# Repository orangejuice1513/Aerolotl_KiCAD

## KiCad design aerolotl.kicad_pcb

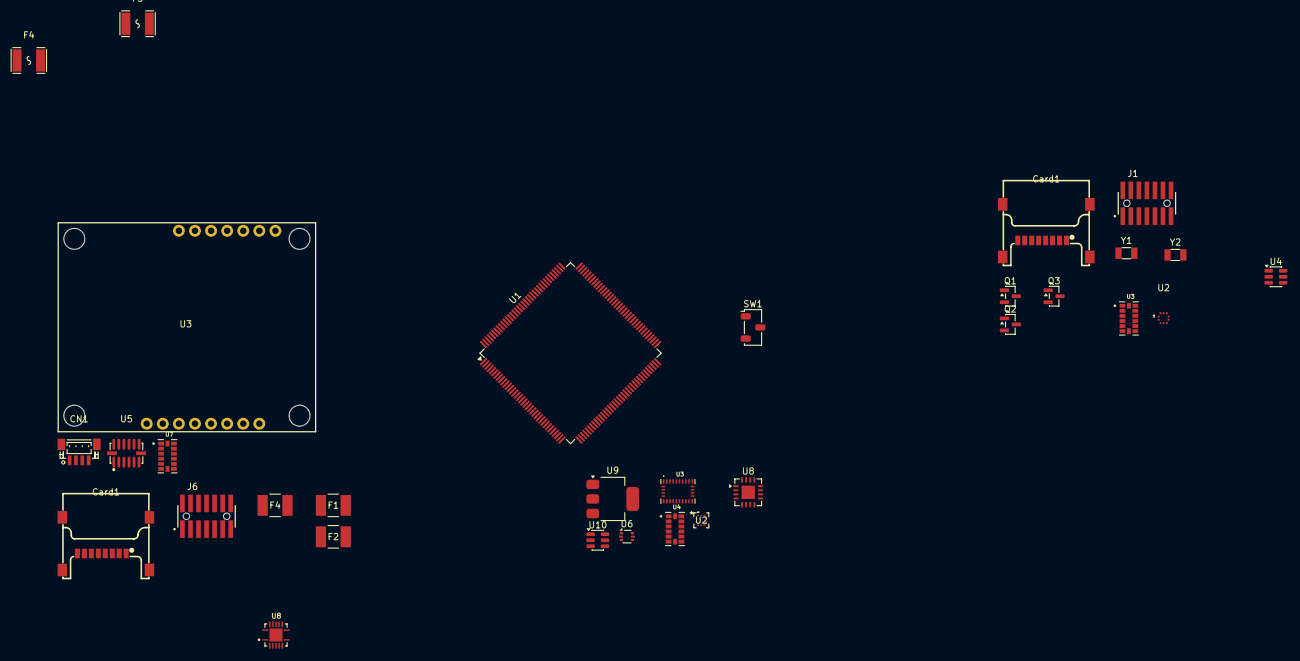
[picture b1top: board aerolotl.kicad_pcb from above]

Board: 2 copper layers, 31 parts (0 on the bottom side), 33 nets, no tracks yet.

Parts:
CN1: StemmaQT; CONN-SMD_BM04B-SRSS-TB
Card1: TF-102-15_SD_read; TF-SMD_TF-102-15
Card1#2: TF-102-15; TF-SMD_TF-102-15
F1, F2, F4#2: 1812L150/24MR; FUSE_1812L150&slash_24_LTF
F3, F4: 1812L300/24SLER; F1812
J1: SWD; SAMTEC_FTSH-107-01-L-DV-K-A
J6: FTSH-107-STDC14; SAMTEC_FTSH-107-01-L-DV-K-A
Q1, Q2, Q3: AO3400A; SOT-23
SW1: SW_Nidec_CAS-120A1; Nidec_Copal_CAS-120A
U1: STM32H755ZIT6; LQFP-144_20x20mm_P0.5mm
U2: BMP581; LGA-10_L2.0-W2.0-P0.50-TL_BMP581
U2#2: BMP581; QFN10_BMP581_BOS
U3: BNO085; IC_BNO085
U3#2, U4#2: ADXL345BCCZ-RL7; PQFN80P500X300X100-14N
U3#3: SparkfunM9N
U4, U10: LMR51430XFDDCR; SOT-23-6
U5: ADXL375BCCZ-RL7; LGA-14_L5.0-W3.0-P0.80-BL
U6: USBLC6-2P6; SOT-666
U7: ADXL345BCCZ-RL7; ADXL345
U8: TPS54620RGYR; TPS54620_7v4buck
U8#2: FT230XQ; QFN-16-1EP_4x4mm_P0.65mm_EP2.1x2.1mm
U9: AMS1117-3.3; SOT-223-3_TabPin2
Y1: 25M; Crystal_SMD_3215-2Pin_3.2x1.5mm
Y2: 32k768; Crystal_SMD_3215-2Pin_3.2x1.5mm

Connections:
+3V3: Card1.4 (VDD), Card1#2.4 (VDD), J6.03, SW1.3 (A), U1.7 (VDD), U1.8 (VBAT), U1.13 (VDD), U1.16 (VDDSMPS), U1.19 (VDD), U1.32 (VDD), U1.42 (VDD), U1.56 (VDD), U1.70 (VDDLDO), U1.71 (VDD), U1.79 (VDD), U1.90 (VDD50_USB), U1.91 (VDD33_USB), U1.92 (VDD), U1.105 (VDDLDO), U1.106 (VDD), U1.119 (VDD), U1.129 (VDD), U1.142 (PDR_ON), U1.143 (VDDLDO), U1.144 (VDD), U3#3.6 (3V3), U3#3.11 (3V3)
+7V4_SERVO: F3.1, F4.1
+12V: U4.3 (VIN), U4.5 (EN)
+12V_ARM: F1.2, F2.2
/Debugger/T_SWCLK: J1.06, J6.06, U1.107 (PA14)
/Debugger/T_SWDIO: J1.04, J6.04, U1.102 (PA13)
/Debugger/T_SWO: J1.08, J6.08, U1.130 (PB3)
/Debugger/T_VCP_RX: J1.14, J6.14, U1.98 (PA9)
/Debugger/T_VCP_TX: J1.13, J6.13, U1.99 (PA10)
/IMUs/ADXL345.CS: U3#2.7 (~CS), U7.7 (~CS)
/IMUs/ADXL345.SCLK: U1.44 (PA5), U2.2 (SCK), U3#2.14 (SCL/SCLK), U5.14 (SCL/SCLK), U7.14 (SCL/SCLK)
/IMUs/ADXL345.SDI: U1.45 (PA6), U2.5 (SDO), U3#2.13 (SDA/SDI/SDIO), U5.12 (SDO/ALTADDRESS), U7.13 (SDA/SDI/SDIO)
/IMUs/ADXL345.SDO: U1.46 (PA7), U2.4 (SDI), U3#2.12 (SDO/ALT_ADDRESS), U5.13 (SDA/SDI/SDIO), U7.12 (SDO/ALT_ADDRESS)
/MCU/BOOT0: SW1.2 (B), U1.135 (BOOT0)
/MCU/HS_OSC_A: U1.25 (PH0), Y1.1
/MCU/HS_OSC_B: U1.26 (PH1), Y1.2
/MCU/LS_OSC_A: U1.10 (PC14), Y2.2
/MCU/LS_OSC_B: U1.11 (PC15), Y2.1
/MCU/RESET: J6.12, U1.27 (NRST)
/MCU/SDMMC1.CK: Card1.5 (CLK), Card1#2.5 (CLK), U1.111 (PC12)
/MCU/SDMMC1.CMD: Card1.3 (CMD), Card1#2.3 (CMD), U1.114 (PD2)
/MCU/SDMMC1.D0: Card1.7 (DAT0), Card1#2.7 (DAT0), U1.95 (PC8)
/MCU/SDMMC1.D1: Card1.8 (DAT1), Card1#2.8 (DAT1), U1.96 (PC9)
/MCU/SDMMC1.D2: Card1.1 (DAT2), Card1#2.1 (DAT2), U1.109 (PC10)
/MCU/SDMMC1.D3: Card1.2 (CD/DAT3), Card1#2.2 (CD/DAT3), U1.110 (PC11)
/MCU/USB_D_M: U1.100 (PA11), U6.6 (I/O1)
/MCU/USB_D_P: U1.101 (PA12), U6.4 (I/O2)
/MCU/VFBSMPS: U1.17 (VFBSMPS), U1.68 (VCAP), U1.103 (VCAP), U1.140 (VCAP)
/Power/P_VBUS: U6.5 (VBUS), U9.3 (VI)
/USB to UART/VCCIO: U8#2.1 (VCCIO), U8#2.8 (3V3OUT), U8#2.9 (~RESET)
GND: CN1.0, CN1.1, Card1.6 (VSS), Card1.9 (SHELL), Card1.10 (SHELL), Card1.11 (SHELL), Card1.12 (SHELL), Card1#2.6 (VSS), Card1#2.9 (SHELL), Card1#2.10 (SHELL), Card1#2.11 (SHELL), Card1#2.12 (SHELL), J1.05, J1.07, J6.05, J6.07, Q1.2 (S), Q2.2 (S), Q3.2 (S), U1.6 (VSS), U1.12 (VSS), U1.14 (VSSSMPS), U1.18 (VSS), U1.33 (VSS), U1.34 (VSSA), U1.41 (VSS), U1.55 (VSS), U1.69 (VSS), U1.80 (VSS), U1.89 (VSS), U1.104 (VSS), U1.118 (VSS), U1.128 (VSS), U1.141 (VSS), U2.3 (VSS), U2.8 (VSS), U2.9 (VSS), U3#2.2 (GND), U3#2.4 (GND), U3#2.5 (GND), U3#3.5 (GND), U3#3.9 (GND), U4.1 (GND), U4#2.2 (GND), U4#2.4 (GND), U4#2.5 (GND), U5.2 (GND), U5.4 (GND), U5.5 (GND), U5.11 (RESERVED), U6.2 (GND), U7.2 (GND), U7.4 (GND), U7.5 (GND), U7.11 (RESERVED_11), U8#2.3 (GND), U8#2.13 (GND), U8#2.17 (GND), U9.1 (GND)
VCC: CN1.2, F4#2.2
VDD: U3#2.1 (VDD_I/O), U3#2.6 (VS), U5.1 (VDDI/O), U5.3 (RESERVED), U5.6 (VS), U7.1 (VDD_I/O), U7.3 (RESERVED_3), U7.6 (VS)

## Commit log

2026-03-29 solved reverse polarity w pmos and tvs clamp
2026-03-30 replaced bno w bmi
2026-03-31 updated pyrocircuit with components and TO-252-2 footprint for mosfets. not done with sim
2026-04-01 changed nmos and 2 resistors, 3 tests passed
2026-04-01 removed sense continuity circuit, all tests passed
2026-04-02 added ematch continuity part of circuit, tested
2026-04-04 finalized ematch sensing ciruit, not simmed
2026-04-05 final: passed all tests.
